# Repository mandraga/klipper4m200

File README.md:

# klipper4m200

A replacement firmare for the Zortrax M200+ 3D printer.

This firmware is based on Debian/Armbian and allows to install klipper on the m200+.
There is no comming back once the microcontroller is flashed.

# Building steps

Update the submodules, or get them separately.
* Armbian build
* u-boot
* sunxi-tools

## Access the internal single board computer

You need:
* a serial port on the UART0 J5 connector for the u-boot and Linux serial console.
* a special USB-A to USB-A cable with no 5V connexion to be able to use the FEL mode.

At boot, press '2' on the serial console, it will start in FEL mode.
You should see this on "dmesg -w":
```
ID 1f3a:efe8 Allwinner Technology sunxi SoC OTG connector in FEL/flashing mode
```
Then, using sunxi-tools, you can upload a uboot image like this:
```
sunxi-tools$ sudo ./sunxi-fel uboot ../u-boot/u-boot-sunxi-with-spl.bin
```
It starts uboot and you can browse files and dump data.

Then you can use this uboot prompt to load the dtb and the kernel, then boot Armbian from the usb stick.

Once in Linux, you can:
- dump the original disk image on the usb stick.
- dump the vendor u-boot env
- write your u-boot-env
- write u-boot-dtb.bin to the FAT16 partition

## Download the image

Compile u-boot with build_m200.sh from the bootstage folder in this repo, run it in the u-boot fork repo.
Create an Armbian full image using the lime-A33 board using the armbian_build repo.
DD it on /dev/sdx2 where sdx is your usb stick (or edit uboot command to use sdx1 instead).
Do not forget to include linux headers and to enable the touchscreen (see linux.md).
In armbian_build:
```
./compile.sh INSTALL_HEADERS=yes
```

## At first boot from FEL mode

Look at usb.md or progress.md to see how to load the kernel from u-boot.

Install the new u-boot env and mainline uboot binary on the emmc such as to automaticly boot from the USB drive.
The original emmc is not that much altered, only the env. You can resore it with a backup file or in vendor u-boot console.

### Get the network

* On version 2.1, Linux should detect the ethernet usb adapter on the USB port.
  Version 2.1 has two usb ports.
* On version 1.1, the USB0 trace must be cut and a posrt soldered to boot from USB. You need to connect some ethernet 
adapter to an usb hub.
  Version 1.1 has only one USB port on the front.

Then connect your printer to the network.

### Install klipper

Follow this tutorial
https://travis90x.altervista.org/armbian-first-boot-and-install-klipper/

```
git clone https://github.com/dw-0/kiauh.git
./kiauh/kiauh.sh
```
It will install everything klipper related and build the firmware.

### Flash the microcontroller and start Klipper

See the Readme in the MCU folder, you need an ST-Link programmer to mass erase the chip.

## Klipper config

rpanfili has already configured klipper for zortrax M200 but for an SK200 MCU board.
However the geometry and a lot of stock parameters are already in his configuration.

Zortrax has published a Marlin port for the M200.
By looking at the commits, and the work done in the zmxxxp-re repository, I could find the MCU pinouts in "pins_ZORTRAX_M200.h" to configure the klipper MCU firmware.
Be carefull whith the X, Y axis stops, they are not the same depending on verison 1.1 or 2.2.

The configuration in this repo is the rpanfili one, modified for the Zortrax MCU board instead of the SK1.4.

## Calibration and tuning

https://ellis3dp.com/Print-Tuning-Guide/
https://github.com/OrcaSlicer/OrcaSlicer/wiki/Calibration

The ZABS spec
https://cf.zortrax.com/wp-content/uploads/2020/09/Z-ABS_2_Technical_Data_Sheet_eng.pdf

PID tuning at different fan speeds and in GCODE:
https://www.youtube.com/watch?v=USvg6D0cXE4

## Start printing

If everything went fine, you can connect to Mainsail or Fluid web interfaces copy the klipper configuration and start configuring the bed level.
Then, because it is klipper, you must run calibration towers with your filaments and tweak orcaslicer prior to begin printing. That's what's lost in the process but you have control and can use any filament.

## About

This work lasted from october 2025 to April 2026 and was much more difficult than planed, given that the device tree of this thing is really complex, the EMMC is really touchy, and the screen had no driver.
The boot process investigation led to 4 bricks, and needed resoldering a new programmed EMMC to save the boards.
Since then, I tryed to port an ezeetab 96Q10 A-33 Andorid tablet to linux and it was quicker (a week) and also helped to progress on this project.

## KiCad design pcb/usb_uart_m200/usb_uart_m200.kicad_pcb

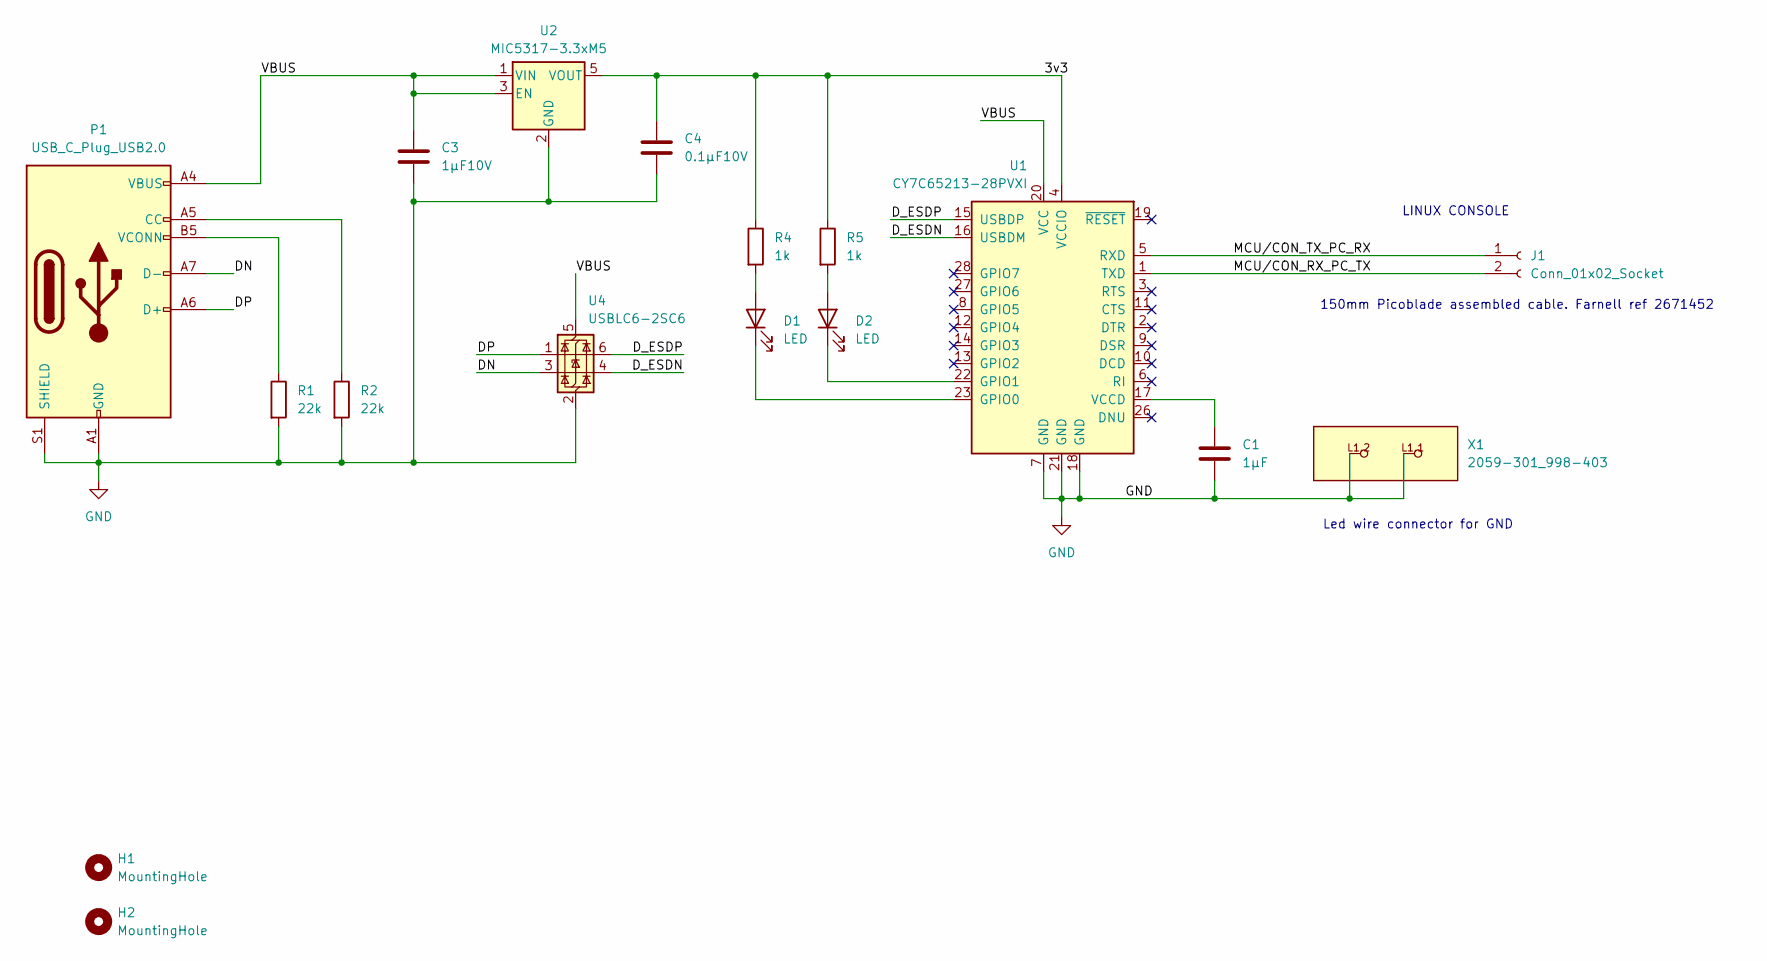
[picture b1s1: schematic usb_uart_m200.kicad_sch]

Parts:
C1: 1µF; C_0805_2012Metric
C3: 1µF10V; C_0805_2012Metric
C4: 0.1µF10V; C_0805_2012Metric
D1, D2: LED; LED_0805_2012Metric_Pad1.15x1.40mm_HandSolder
H1, H2: MountingHole; MountingHole_2.2mm_M2_ISO7380
J1: Conn_01x02_Socket; Molex_PicoBlade_53047-0210_1x02_P1.25mm_Vertical; farnell 9733051
P1: USB_C_Plug_USB2.0; USB_C_Receptacle_G-Switch_GT-USB-7010ASV; farnell 3777659
R1, R2: 22k; R_0805_2012Metric; farnell 2073691
R4, R5: 1k; R_0805_2012Metric
U1: CY7C65213-28PVXI; SSOP-28_5.3x10.2mm_P0.65mm; farnell 2772892
U2: MIC5317-3.3xM5; SOT-23-5; farnell 2920683
U4: USBLC6-2SC6; SOT-23-6; farnell 1269406
X1: 2059-301_998-403; P-2059-301_998-403; farnell 2452830

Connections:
/3v3: C4.1, R4.1, R5.1, U1.4 (VCCIO), U2.5 (VOUT)
/DN: P1.A7 (D-), U4.3 (I/O2)
/DP: P1.A6 (D+), U4.1 (I/O1)
/D_ESDN: U1.16 (USBDM), U4.4 (I/O2)
/D_ESDP: U1.15 (USBDP), U4.6 (I/O1)
/MCU/CON_RX_PC_TX: J1.2, U1.1 (TXD)
/MCU/CON_TX_PC_RX: J1.1, U1.5 (RXD)
/VBUS: C3.1, P1.A4 (VBUS), P1.A9 (VBUS), P1.B4 (VBUS), P1.B9 (VBUS), U1.20 (VCC), U2.1 (VIN), U2.3 (EN), U4.5 (VBUS)
GND: C1.2, C3.2, C4.2, P1.A1 (GND), P1.A12 (GND), P1.B1 (GND), P1.B12 (GND), P1.S1 (SHIELD), R1.2, R2.2, U1.7 (GND), U1.18 (GND), U1.21 (GND), U2.2 (GND), U4.2 (GND), X1.L1.1, X1.L1.2
unnamed: D1.2 (A), R4.2
unnamed: D1.1 (K), U1.23 (GPIO0)
unnamed: D2.2 (A), R5.2
unnamed: D2.1 (K), U1.22 (GPIO1)
unnamed: P1.A5 (CC), R2.1
unnamed: P1.B5 (VCONN), R1.1
unnamed: C1.1, U1.17 (VCCD)

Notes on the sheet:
LINUX CONSOLE
Led wire connector for GND
150mm Picoblade assembled cable. Farnell ref 2671452

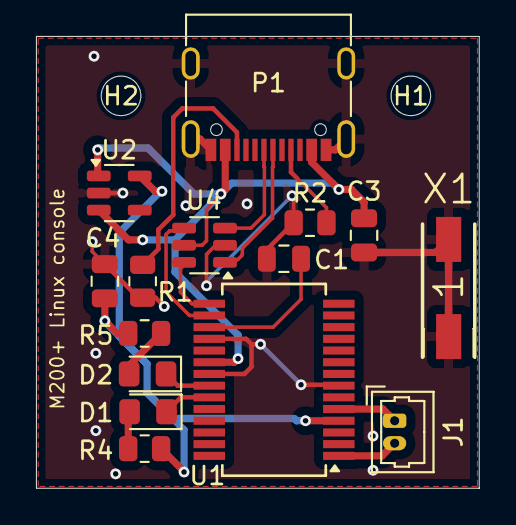
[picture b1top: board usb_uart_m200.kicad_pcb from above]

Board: 2 copper layers, 24.6 x 25.1 mm, 17 parts (0 on the bottom side), 16 nets.

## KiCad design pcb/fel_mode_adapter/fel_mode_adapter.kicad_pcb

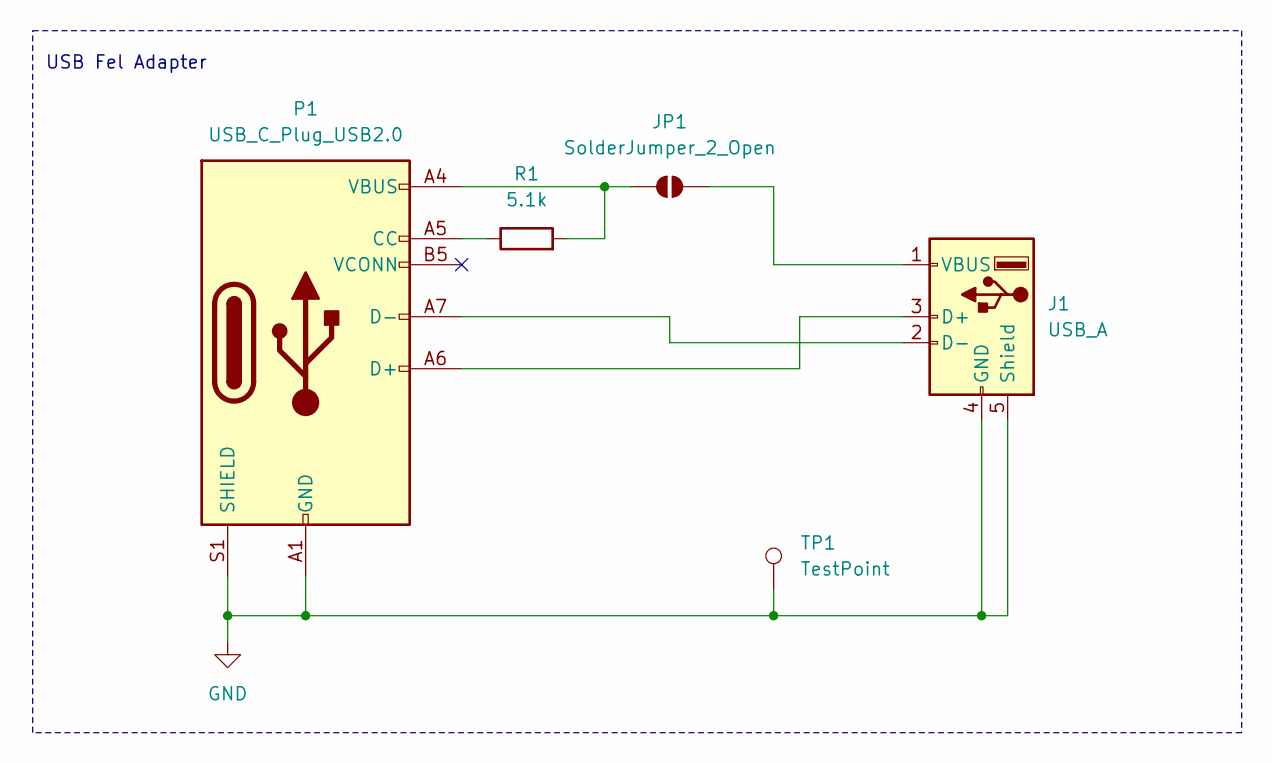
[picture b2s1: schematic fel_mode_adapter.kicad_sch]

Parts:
J1: USB_A; USB_A_Molex_48037-2200_Horizontal; farnell 2313729
JP1: SolderJumper_2_Open; SolderJumper-2_P1.3mm_Open_TrianglePad1.0x1.5mm
P1: USB_C_Plug_USB2.0; USB_C_Receptacle_G-Switch_GT-USB-7010ASV; farnell 3777659
R1: 5.1k; R_0805_2012Metric
TP1: TestPoint; TestPoint_Pad_D1.0mm

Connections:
GND: J1.4 (GND), J1.5 (Shield), P1.A1 (GND), P1.A12 (GND), P1.B1 (GND), P1.B12 (GND), P1.S1 (SHIELD), TP1.1
unnamed: J1.3 (D+), P1.A6 (D+)
unnamed: J1.2 (D-), P1.A7 (D-)
unnamed: J1.1 (VBUS), JP1.2 (B)
unnamed: JP1.1 (A), P1.A4 (VBUS), P1.A9 (VBUS), P1.B4 (VBUS), P1.B9 (VBUS), R1.2
unnamed: P1.A5 (CC), R1.1

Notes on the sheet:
USB Fel Adapter

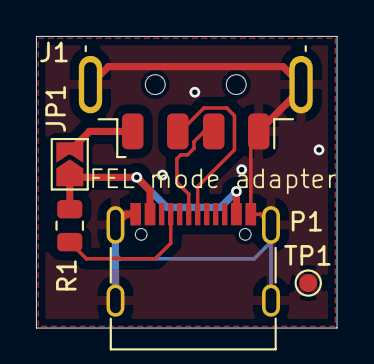
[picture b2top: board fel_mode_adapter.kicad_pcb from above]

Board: 2 copper layers, 16.7 x 16.2 mm, 5 parts (0 on the bottom side), 6 nets.

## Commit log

2025-10-21 Uboot access scripts.
2025-10-24 Schematics of the uart board
2025-10-24 Fex files from the first dump on the board where the Wifi is on USB.
    The first fex is the good one with the proper LCD driver.
2025-10-24 Script to dump the original image and pinouts
    Dump the emmc to backup it.
2025-11-15 Some scripts to start the m200+ on the usb storage.
2025-11-15 Armbian image file modification script to add everything needed to boot on Zortrax m200+
2025-11-15 Add the first 4k of the sunxi u-boot env partition.
    The bootdelay parameter has been changed to 2 in order to access the
    sunxi u-boot prompt.
2025-11-19 Add MarlinConfigurations as a submodule
2025-11-19 MCU specification document
2025-11-19 Changed the rpanfili configuraiton to use the original MCU.
2025-11-24 Some work on the driver.
2025-11-26 Compiling LCD driver
2025-11-26 Cleanup the makefile.
2025-12-10 Driver rework
    Initialisation bytes taken from the lcd.ko module binary content on the
    vendor linux plus some comparisons and fixes.
2025-12-10 A couple of name changes on the lcd driver.
2025-12-14 Adding katapult as a submodule.
2025-12-14 Updating the MCU pinout documents.
2025-12-16 Documentation about katapult
2025-12-16 First draft of the MCU programmer / linux serial console.
2025-12-16 Routing
    Separated the uart from the FEL adapter board.
    Adds a led wire connector for the ground pin.
2026-01-08 Fix the board: add a regulator and farnelle references. Add a pull up on boot0
2026-01-08 Fix on the usb uart power, it uses vbus.
2026-01-12 Add a picture showing how the EMMC boot0 partition was unbricked.
    A new EMMC was flashed using a chip programmer over USB and then
    soldered on the board.
    Not everything was clean owever, but booting, an image copy was dd on
    emmcblk2 from the booted linux.
2026-01-12 This is the binary image used to chainload u-bbot mainline from the old u-boot sunxi.
    dd this file to /dev/mmcblk2p5 to chainload u-boot.
2026-01-15 Cleanup
2026-01-15 Mainline driver
2026-01-15 Documentation afte a cleanup
2026-01-15 An ssh script for convenience
2026-01-16 First draft of a vedor compatible programmer.
2026-01-16 The zortrax bootloader is answering to the V1 protocol
2026-01-17 Compilation error cleanup
2026-01-17 A gitignore file
2026-01-23 The lcd screen works.
    This was quite a lot of work. Nice that it finally works, tested on
    Armbian non minimal image.
2026-01-23 Removed the DEBUG header from the serial port board since the MCU needs a stlink total erase.
    Adds the screen capture of the configuration in Katapult menuconfig.
2026-01-23 Adds dev log with information mostly about the boot process.
    Gives the sumary of all the command lines and information used to boot
    Linux in there.
2026-01-23 Update the uboot info
    Gives the link to the fork for the Zortrax m200 u-boot
2026-01-23 Droping the vendor bootloader protocol investigation.
    It is so obfuscated and therefore we will use klipper, if you flash
    katapult there is no going back.
    And for your next printer, think about a Voron.
2026-01-23 Information on flashing the MCU
    Logs from flashing katapult and kliper on the MCU.
2026-01-25 Klipper configuration files
2026-01-25 The Z Min pin is not the same on the plus version.
2026-01-25 Adding the zmxxp-re documentation repo to the submodules.
2026-01-25 Klipper configuration
    FANS, X, Y Extruder steppers, temperature sensors and RGB leds are
    working.
2026-01-26 Adding the u-boot fork as a submodule
2026-01-26 Adding a BOM file for the extra stuff not soldered on the board.
2026-01-26 Some cleanup before sharing.
2026-01-26 Remove an obsolete documentation.
2026-01-27 Removing the non working initialisation data before working on sapazzimoto parameters
2026-01-27 Update the documentation
2026-01-27 Test spazzimoto driver and try to mix it wih mine
    While the drivers are really close, and both work, using the spazzimoto
    parameters in mine gives a segfault.
    Seems that removing MIPI_DSI_MODE_VIDEO_BURST solves the shifted screen
    problem.
2026-01-27 Rename comments such as a not so skilled user doe not kill his system.
    Replace sda with sdx in the documentation.
2026-01-27 Screnn oriantation documentation for KlipperScreen.
2026-01-27 Removed the SPAZZIMOTO_TIMINGS define, because it is not compatible.
    It is a driver or the other, but mixing them does not work.
    Sapzzimoto driver init sequence came from microtech and hence is not a
    guess work like here.
2026-01-27 This script is not needed anymore. The lcd driver works.
2026-01-28 Adding the firmware working with katapult
    Green light is katapult boot
    Blue light is klipper
2026-01-28 Use requestbottloader.sh to restart in katapult bootloader mode.
2026-02-23 ZStop, Probe, Filament sensor, ZStepper
    My Z axis has a problem. Until I try on another printer, I do not know
    what is going on. I had to increase the values on the Z stepper compared
    to the theoretical 8mm/turn.
    The Zstop is at the botton, and the probe being the nozzle is at the top
    but the "probe" command looks for it on the bottom.
2026-02-26 Got the Z axis working with the optical sensor stop.
    The probe sensor is not good enough on the M200, it must be perfectly
    clean on bed leveling but we cannot expect to be clean all the time.
2026-03-04 The tepearatures and PID are configured.
    3V3 on the thermistors was causing problems, the software uses 5V by
    default.
    Ran the PID tests on the hardware.
2026-03-04 Adds a GND test point to the FEL mode adapter.
2026-03-04 Lib files for the usb uart.
2026-03-07 Fixing speed on the extruder.
    It is diameter * Pi: I entered 9mm x Pi.
    It rotates more slowly.
2026-03-08 adds Print-Tuning-Guide as submod + extruder qualibrated and fixes in macros
2026-03-08 Fixing the Z axis rattling (after greasing and tightening things up)
2026-03-11 PID tuning with the fan on
    First tuning cube print with a prime line, ZABS, 260°C, fan at 40%, and
    bed at 55°C then 78°C with the regular M200 plus printing head.
    The Z acceleration was still aproble during print, it was not noticed
    during Z axis homing. It still does some noise during the print since
    acceleration and speed had to be decreased again.
    The 100% fan heater calibration would fail. So it is strugling at 50%
2026-03-18 Adding the boot0 image, just as a safety.
    Boot0 is a protected sector, the only thing able to load the FEL monde
    on the Zortrax M200.
    If like me you end up destroying it, and having to program a new one
    using a MMC programmer and soldering the chip.
2026-03-18 Original Script.bin in compiled form.
    This file is located somewhere after the sector 38192.
    The strings contained in this file can help locate it on other sunxi
    systems.
2026-03-18 Updating u-boot
    minor fix on the touchscreen
2026-03-18 Prime line gcode change
    The original gcode was extruding over an already created line, thus
    cloging the nozle.
2026-03-18 Documenting my second failure with boot0
    I cofused Boot0 from the start with a separate parition, and I managed
    to destroy it a second time. And the soldering of the new chip half
    failed, leaving me only with Boot0.
    To my defense, this is not well documented. Like the secondary u-boot at
    0x12A6000
2026-03-18 Rotate the screen using this xorg parameter file.
2026-03-18 Fixing a touchscreen issue
    The touchscreen driver was not packed during the Armbian image creation.
    So I added the instructions to build it on the target like the LCD
    driver.
2026-03-19 Bootenv to chainload uboot mainline from the stock u-boot
    However the chainloaded uboot won't have acess to the EMMC. It now has
    acess from FEL mode but not after chainload.
2026-03-26 Adding the plans of an A33 board as submodule.
2026-03-26 Freecad 1.1 drawing to mount a dragon burner on the Zortrax m200
    I have a printer without nozzle and another one with a cheap replacement
    nozzle. I will place a Rapido and a TZ6 on a dragon burner head.
2026-03-26 Updating the dragon burner adapter
2026-03-31 Adding a pocket for cables on the side. Changing the screws to 35mm for more rigidity.
2026-03-31 Changed the dragon burner mount
    The last change did not work, because the screws crossed the same path.
    They could not fit together.
    I replaced the 6mm holes with a tiny hole to fit the hex key, and a
    pocket to insert a smaller 6mm flat head hex screw
2026-03-31 Improvements for the dragon burner attachment.
    Removes a side of the mount to pass the cables. Increases slightly the
    pocket holes for the 3M 6mm screws.
    Add a washer project because the TZ-6 nozzle was wobling. His screws
    were pressing against the fan metal while not pressing on the plastic
    mount.
2026-04-05 Adds an extruder cover to fit the dragon burner mod wires if they are longer than needed.
2026-04-05 Some dev diary update
    Removing dangerous commands from the diary (who can brick the board).
2026-04-06 Cleanup and adding mecanical stuff
    Cleanup in the documentation.
    Adding the dragon bruner mount, a bl touch mount.
2026-04-09 U-boot update for EMMC cases.
2026-04-09 Updates on the dragon burner adaptation.
2026-04-09 Adding a readme to the sunxi uboot env files.
2026-04-09 Washers stl file for TZ-V6-2 hotend.
    Without them, the hotend is moving.
2026-04-09 Some edits on pinouts
2026-04-09 Got the stepper Z configuraiton right.
2026-04-09 Updating the Readme
2026-04-11 Adding a submodule of a tool to embedd uboot in sunxi data format
    I developped a tool to be able to start u-boot proper without touching
    the boot0 partition.
2026-04-12 Adds a service to restart the panel driver
    As we chainload something goes wrong with the panel that is not present
    when booting through FEL mode.
    A service restarts the panel module.
    Also a ton of documentation updates. I found out a way to unbrick
    without replacing the EMMC, by using a capacitor on EMMC-CLK.
2026-04-12 DOC: dragon burner configurations
2026-04-12 How to go in fel mode from a chainloaded u-boot mainline.
    Taken from the Boot0 source code.
2026-04-22 PCB sources after production
2026-04-22 Update submodules
2026-05-04 Updating the uart and fel mode adapter after soldering it.
    Manufacturing shiwed the pcb to be too large and the gnd wire connector
    too close to the uart connector. The farnell reference resistor on the
    fel mode adapter was of the wrong foorprint.
2026-05-05 Updatin u-boot
    The OTG port can be used to boot linux from USB.
2026-05-13 Add klicky adapter for eva-2.2-klicky_probe_mount
    eva-2.2-klicky_probe_mount.stl is in
    https://github.com/jlas1/Klicky-Probe.git
